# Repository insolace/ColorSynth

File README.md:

# ColorSynth<br>
MIDI Controlled Light Synthesizer<br>
Created by Eric Bateman

ColorSynth is a MIDI controlled sculpture and light synthesizer.  
* Lightning fast strobe and oscillators, written in PIC assembly
* Super bright 3W RGB LEDs
* Power over MIDI, daisy chainable
* Responds to note on and control change events, instant lighting for your MIDI equipped instrument

Visit http://www.colorsynth.com

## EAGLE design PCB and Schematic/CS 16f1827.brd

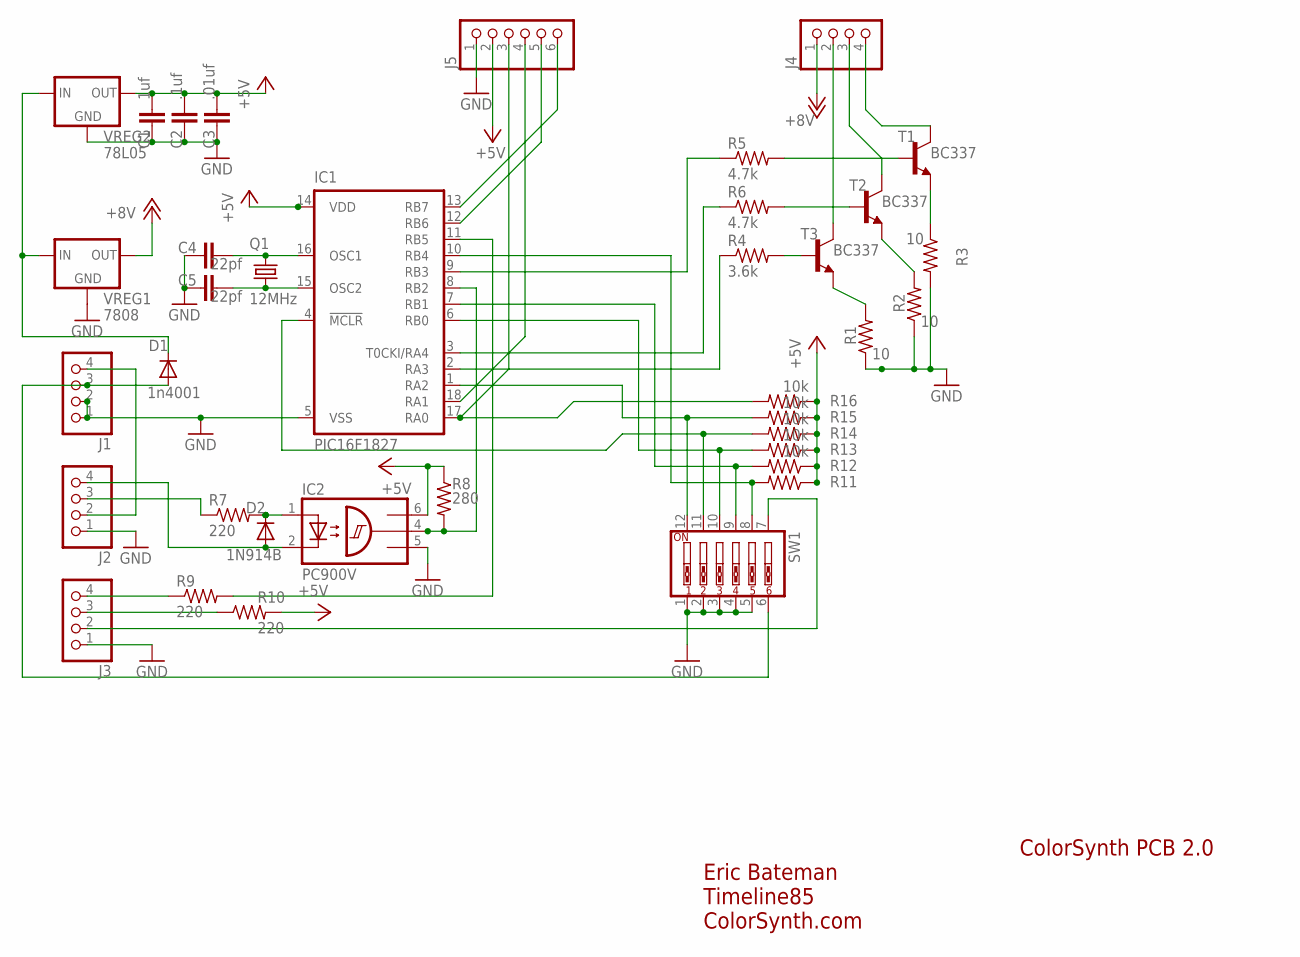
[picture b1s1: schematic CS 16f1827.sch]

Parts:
C1: 1uf; C5B3.5
C2: .1uf; C5B3.5
C3: .01uf; C5B3.5
C4, C5: 22pf; C5B3.5
D1: 1n4001; DO35-10
D2: 1N914B; DO34-7
IC1: PIC16F1827; DIL18
IC2: PC900V; DIL06
J1, J2, J3, J4: PINHD-1X4; 1X04
J5: PINHD-1X6; 1X06
Q1: 12MHz; HC49/S
R1, R2, R3: 10; 0617V
R4: 3.6k; 0207/10
R5, R6: 4.7k; 0207/10
R7, R9, R10: 220; 0207/10
R8: 280; 0207/10
R11, R12, R13, R14, R15, R16: 10k; 0207/10
SW1: SW_DIP-6; EDG-06
T1, T2, T3: BC337; TO92-CBE
VREG1: 7808; 78XXS
VREG2: 78L05; 78LXX

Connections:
5V: C1.1, C2.1, C3.1, IC1.14 (VDD), IC2.6 (VCC), J5.2, R8.1, R10.2, R11.1, R12.1, R13.1, R14.1, R15.1, R16.1, VREG2.OUT
GND: C1.2, C2.2, C3.2, C4.2, C5.2, IC1.5 (VSS), IC2.5 (GND), J1.1, J1.2, J2.1, J3.1, J5.1, R1.1, R2.1, R3.2, SW1.1, SW1.2, SW1.3, SW1.4, SW1.5, VREG1.GND, VREG2.GND
unnamed: D2.A, IC2.2 (C), J2.4
unnamed: D2.C, IC2.1 (A), R7.2
unnamed: R5.2, T1.B
unnamed: IC1.10 (RB4), R11.2, SW1.8
unnamed: R1.2, T3.E
unnamed: C4.1, IC1.16 (OSC1), Q1.1
unnamed: C5.1, IC1.15 (OSC2), Q1.2
unnamed: IC1.2 (RA3), R4.1
unnamed: IC1.12 (RB6), J5.5
unnamed: IC1.3 (T0CKI/RA4), R6.1
unnamed: IC1.9 (RB3), R5.1
unnamed: R6.2, T2.B
unnamed: R4.2, T3.B
unnamed: J4.2, T3.C
unnamed: IC1.7 (RB1), R12.2, SW1.9
unnamed: R2.2, T2.E
unnamed: IC1.6 (RB0), R13.2, SW1.10
unnamed: IC1.4 (!MCLR), R14.2, SW1.11
unnamed: IC1.1 (RA2), R15.2, SW1.12
unnamed: IC1.18 (RA1), J5.4
unnamed: IC1.17 (RA0), J5.3, R16.2
unnamed: R3.1, T1.E
unnamed: IC1.8 (RB2), IC2.4 (OUT), R8.2
unnamed: D1.A, J1.3, SW1.6
unnamed: J4.1, VREG1.OUT
unnamed: IC1.11 (RB5), R9.2
unnamed: IC1.13 (RB7), J5.6
unnamed: J3.4, R9.1
unnamed: J3.3, R10.1
unnamed: J2.3, R7.1
unnamed: J1.4, J2.2
unnamed: J3.2, SW1.7
unnamed: J4.3, T2.C
unnamed: D1.C, VREG1.IN, VREG2.IN
unnamed: J4.4, T1.C

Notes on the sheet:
Eric Bateman Timeline85 ColorSynth.com
ColorSynth PCB 2.0

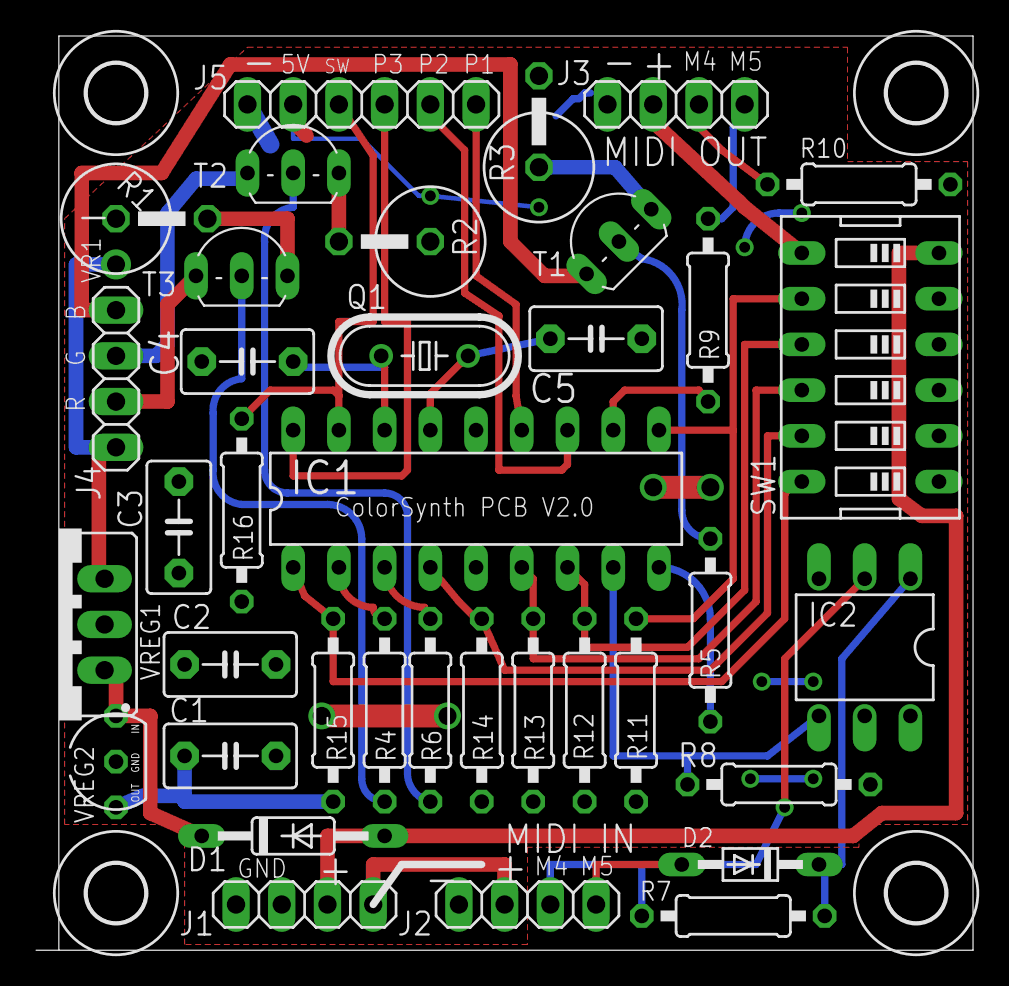
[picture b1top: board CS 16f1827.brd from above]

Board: 2 copper layers, 52.1 x 50.8 mm, 41 parts (0 on the bottom side), 37 nets.

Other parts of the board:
U$1, U$2, U$3, U$4: 3,2

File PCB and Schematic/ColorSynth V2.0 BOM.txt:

ColorSynth PCB/Schematic v2.0 Bill of Materials
Written 2010-01-03 by Eric Bateman
eric@colorsynth.com

Most parts should be easily found at Mouser.com

(1) FIXTURE - available as a kit from ColorSynth.com

(1) Common Anode RGB 3W LED, 350mA max per color.  Voltages can be 1v to 5v for any color, the circuit will compensate
(1) 12V DC power supply, unregulated, 500mA current per ColorSynth
(2) 5 PIN DIN style connectors for MIDI I/O
(1) DC power jack
(1) Power switch (optional).  A selector switch can be used to toggle between external or MIDI power.

(1) Microchip PIC16F1827I/P - IC1
(1) Sharp PC900V optocoupler - IC2
(1) LM7808 DC regulator - VREG1
(1) 78L05 DC regulator - VREG2
(1) 12MHz crystal - Q1
(1) 6 position dip switch, right angle - SW1

(1) 1uf ceramic capacitor - C1
(1) .1uf ceramic capacitor - C2
(1) .01uf ceramic capacitor - C3
(2) 22pf ceramic capacitor - C4, C5

(1) 1N4001 protectio diode - D1
(1) 1N914B diode - D2

(3) 10ohm 1W thru hole resistors - R1, R2, R3
(1) 3.6k ohm 1/4w thru hole resistor - R4
(2) 4.7k ohm 1/4w thru hole resistors - R5, R6
(3) 220 ohm 1/4w thru hole resistors - R7, R9, R10
(1) 280 ohm 1/4w thru hole resistor - R8
(6) 10k ohm 1/4w or 1/8w thru hole resistors - R11, R12, R13, R14, R15, R16

(3) BC337 NPN transistors - T1, T2, T3

(5) .100" spaced pin headers, 4pins each except for J5 which needs 6 pins.

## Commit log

2019-09-16 Source Code and PCB
    Initial upload
2020-03-12 Add graphics
